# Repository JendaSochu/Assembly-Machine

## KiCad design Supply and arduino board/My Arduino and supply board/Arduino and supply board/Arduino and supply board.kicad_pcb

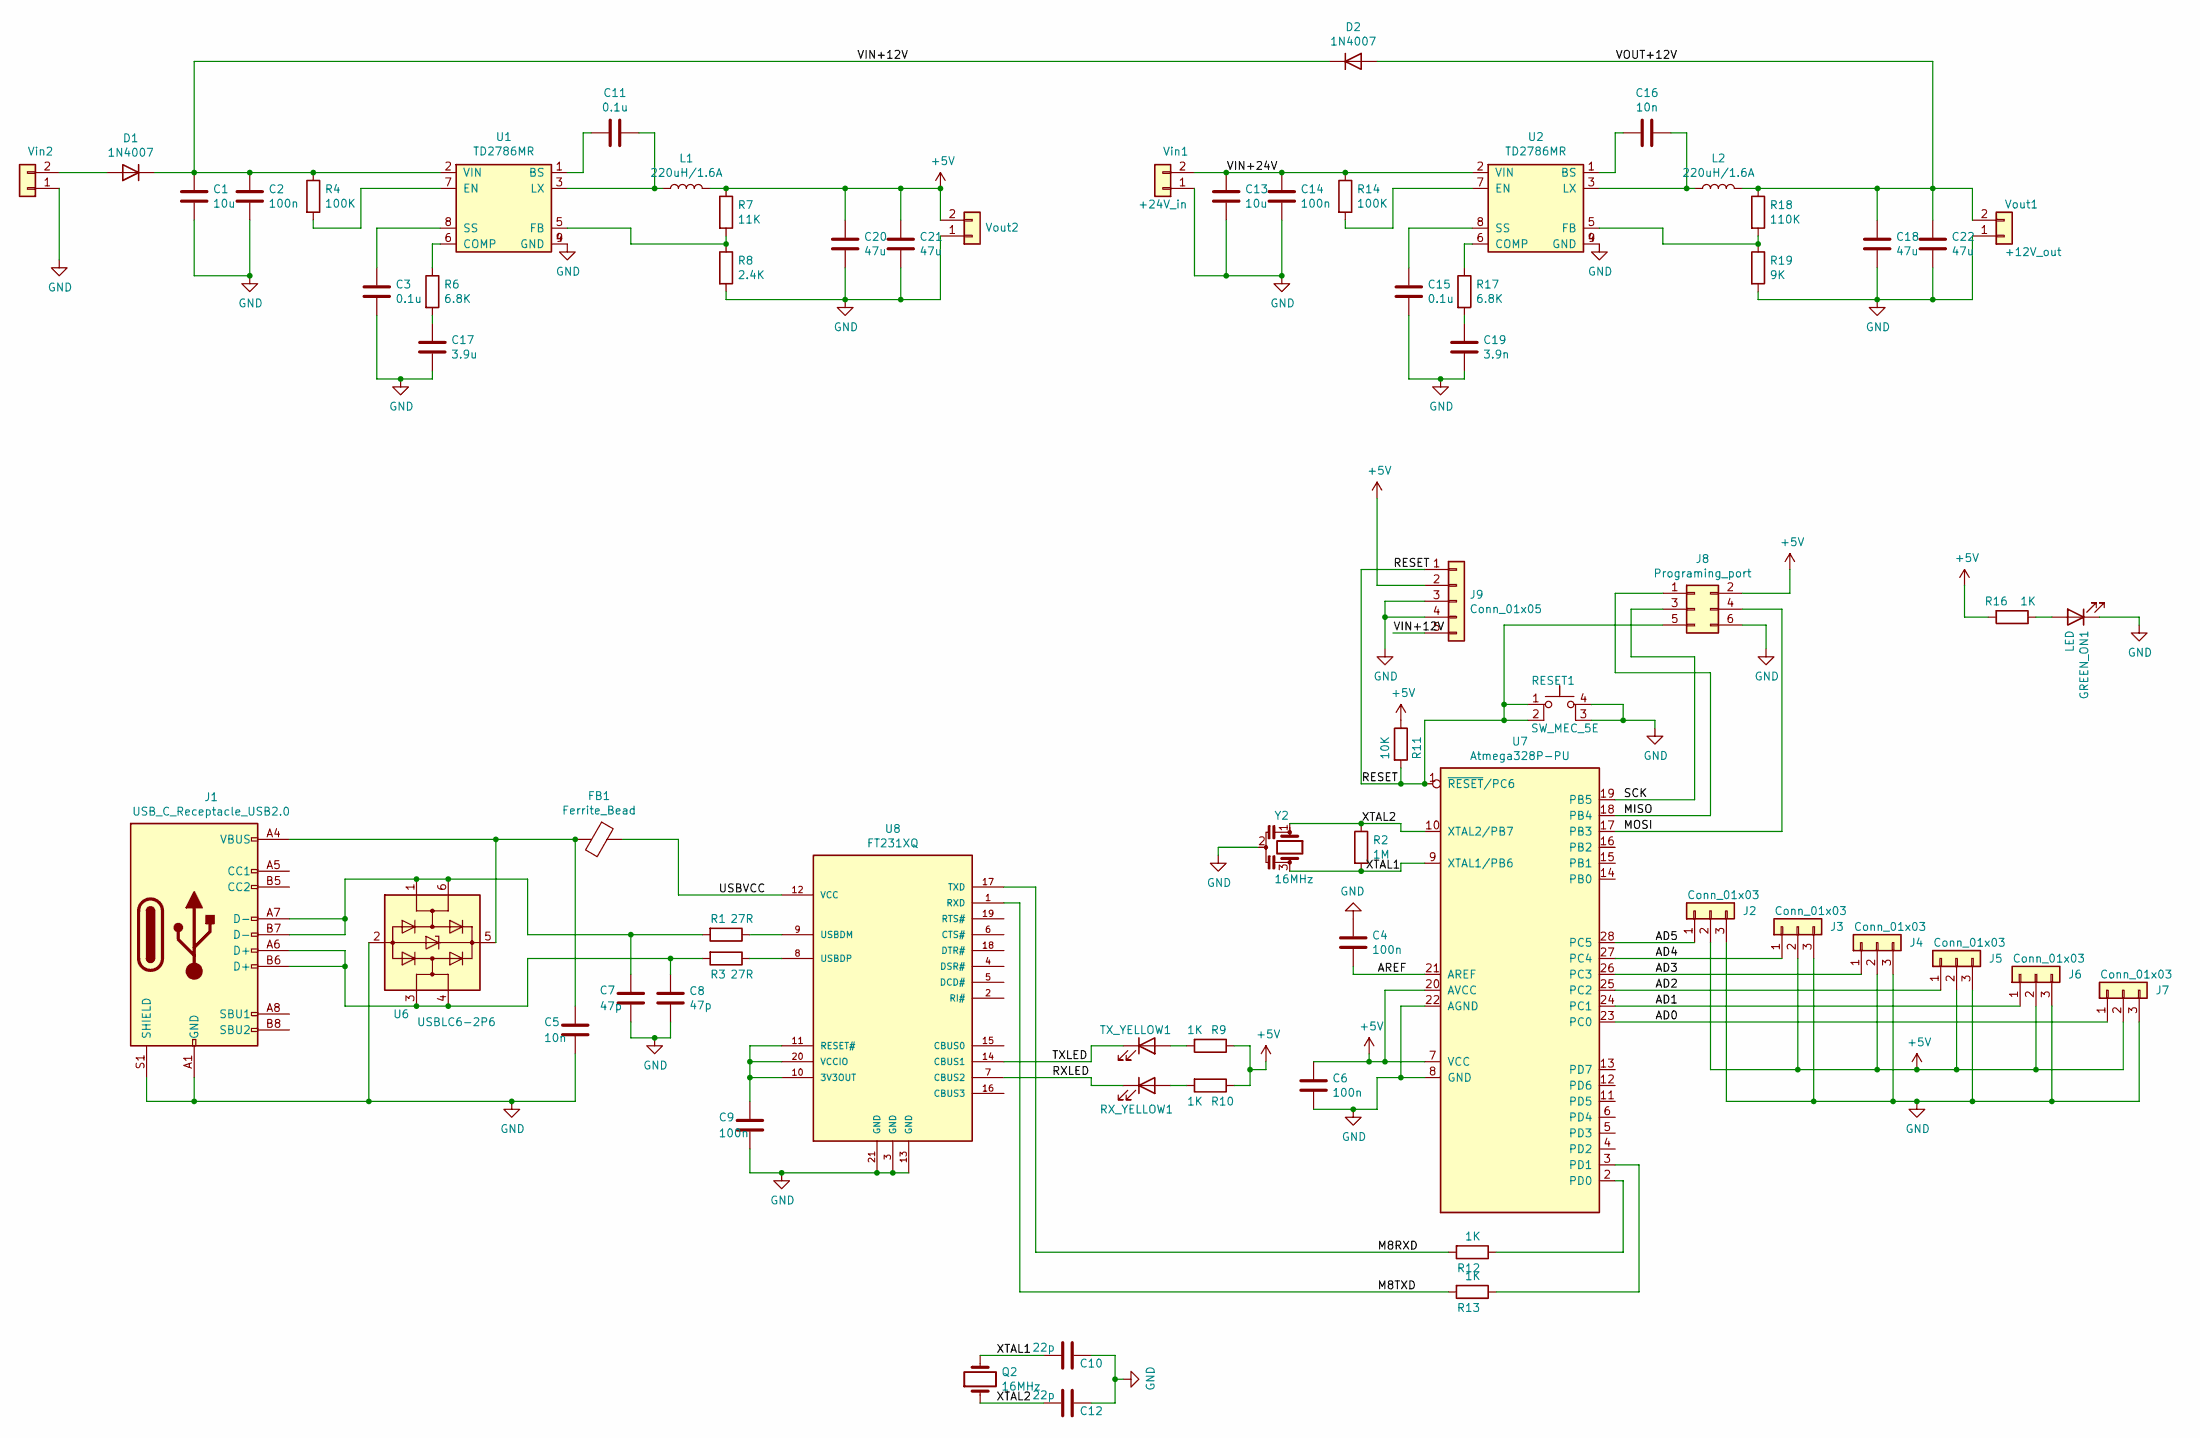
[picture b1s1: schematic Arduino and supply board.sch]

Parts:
C1, C13: 10u; C_0603_1608Metric
C2, C4, C6, C9, C14: 100n; C_0603_1608Metric
C3, C11, C15: 0.1u; C_0603_1608Metric
C5, C16: 10n; C_0603_1608Metric
C7, C8: 47p; C_0603_1608Metric
C10, C12: 22p; C_0603_1608Metric
C17: 3.9u; C_0603_1608Metric
C18, C20, C21, C22: 47u; C_0603_1608Metric
C19: 3.9n; C_0603_1608Metric
D1, D2: 1N4007; D_SMA
FB1: Ferrite_Bead; R_0603_1608Metric
GREEN_ON1: LED; LED_0805_2012Metric
J1: USB_C_Receptacle_USB2.0; USB_C_Receptacle_HRO_TYPE-C-31-M-12
J2, J3, J4, J5, J6, J7: Conn_01x03; PinSocket_1x03_P2.54mm_Vertical
J8: Programing_port; PinHeader_2x03_P2.54mm_Vertical
J9: Conn_01x05; PinHeader_1x05_P2.54mm_Vertical
L1, L2: 220uH/1.6A; L_Wuerth_HCI-1350
Q2: 16MHz; Crystal_HC18-U_Vertical
R1, R3: 27R; R_0402_1005Metric
R2: 1M; R_0402_1005Metric
R4, R14: 100K; R_0402_1005Metric
R6, R17: 6.8K; R_0402_1005Metric
R7: 11K; R_0402_1005Metric
R8: 2.4K; R_0402_1005Metric
R9, R10, R12, R13, R16: 1K; R_0402_1005Metric
R11: 10K; R_0402_1005Metric
R18: 110K; R_0402_1005Metric
R19: 9K; R_0402_1005Metric
RESET1: SW_MEC_5E; SW_DIP_SPSTx02_Slide_6.7x6.64mm_W6.73mm_P2.54mm_LowProfile_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
RX_YELLOW1: LED; LED_0805_2012Metric
TX_YELLOW1: LED; LED_0805_2012Metric
U1, U2: TD2786MR; SOP-8_3.9x4.9mm_P1.27mm
U6: USBLC6-2P6; SOT-666
U7: Atmega328P-PU; TQFP-32_7x7mm_P0.8mm
U8: FT231XQ; QFN-20-1EP_4x4mm_P0.5mm_EP2.5x2.5mm; PARTREV 1.2
Vin1: +24V_in; PhoenixContact_MSTBA_2,5_2-G-5,08_1x02_P5.08mm_Horizontal
Vin2: +12V_in; PhoenixContact_MSTBA_2,5_2-G-5,08_1x02_P5.08mm_Horizontal
Vout1: +12V_out; PhoenixContact_MSTBA_2,5_2-G-5,08_1x02_P5.08mm_Horizontal
Vout2: +5V_out; PhoenixContact_MSTBA_2,5_2-G-5,08_1x02_P5.08mm_Horizontal
Y2: 16MHz; Resonator_SMD-3Pin_7.2x3.0mm

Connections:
+5V: C6.1, C20.2, C21.2, J2.2, J3.2, J4.2, J5.2, J6.2, J7.2, J8.2, J9.2, L1.2, R7.1, R9.1, R10.1, R11.1, R16.2, U7.7 (VCC), U7.20 (AVCC), Vout2.2
/AD0: J7.1, U7.23 (PC0)
/AD1: J6.1, U7.24 (PC1)
/AD2: J5.1, U7.25 (PC2)
/AD3: J4.1, U7.26 (PC3)
/AD4: J3.1, U7.27 (PC4)
/AD5: J2.1, U7.28 (PC5)
/AREF: C4.2, U7.21 (AREF)
/M8RXD: R12.2, U8.17 (TXD)
/M8TXD: R13.2, U8.1 (RXD)
/MISO: J8.1, U7.18 (PB4)
/MOSI: J8.4, U7.17 (PB3)
/RESET: J8.5, J9.1, R11.2, RESET1.1, RESET1.2, U7.1 (~RESET~/PC6)
/RXLED: RX_YELLOW1.1 (K), U8.7 (CBUS2)
/SCK: J8.3, U7.19 (PB5)
/TXLED: TX_YELLOW1.1 (K), U8.14 (CBUS1)
/USBVCC: FB1.1, U8.12 (VCC)
/VIN+12V: C1.1, C2.1, D1.1 (K), D2.1 (K), J9.5, R4.1, U1.2 (VIN)
/VIN+24V: C13.1, C14.1, R14.1, U2.2 (VIN), Vin1.2
/VOUT+12V: C18.2, C22.2, D2.2 (A), L2.2, R18.1, Vout1.2
/XTAL1: C10.1, Q2.2, R2.2, U7.9 (XTAL1/PB6), Y2.3
/XTAL2: C12.1, Q2.1, R2.1, U7.10 (XTAL2/PB7), Y2.1
GND: C1.2, C2.2, C3.2, C4.1, C5.2, C6.2, C7.2, C8.2, C9.2, C10.2, C12.2, C13.2, C14.2, C15.2, C17.2, C18.1, C19.2, C20.1, C21.1, C22.1, GREEN_ON1.1 (K), J1.A1 (GND), J1.A12 (GND), J1.B1 (GND), J1.B12 (GND), J1.S1 (SHIELD), J2.3, J3.3, J4.3, J5.3, J6.3, J7.3, J8.6, J9.3, J9.4, R8.2, R19.2, RESET1.3 (K), RESET1.4 (A), U1.4 (GND), U1.9 (GND), U2.4 (GND), U2.9 (GND), U6.2 (GND), U7.8 (GND), U7.22 (AGND), U8.3 (GND), U8.13 (GND), U8.21 (GND), Vin1.1, Vin2.1, Vout1.1, Vout2.1, Y2.2
unnamed: C3.1, U1.8 (SS)
unnamed: C5.1, FB1.2, J1.A4 (VBUS), J1.A9 (VBUS), J1.B4 (VBUS), J1.B9 (VBUS), U6.5 (VBUS)
unnamed: C7.1, J1.A7 (D-), J1.B7 (D-), R1.2, U6.1 (I/O1), U6.6 (I/O1)
unnamed: C8.1, J1.A6 (D+), J1.B6 (D+), R3.2, U6.3 (I/O2), U6.4 (I/O2)
unnamed: C9.1, U8.10 (3V3OUT), U8.11 (RESET#), U8.20 (VCCIO)
unnamed: C11.1, L1.1, U1.3 (LX)
unnamed: C11.2, U1.1 (BS)
unnamed: C15.1, U2.8 (SS)
unnamed: C16.1, L2.1, U2.3 (LX)
unnamed: C16.2, U2.1 (BS)
unnamed: C17.1, R6.2
unnamed: C19.1, R17.2
unnamed: D1.2 (A), Vin2.2
unnamed: GREEN_ON1.2 (A), R16.1
unnamed: R1.1, U8.9 (USBDM)
unnamed: R3.1, U8.8 (USBDP)
unnamed: R4.2, U1.7 (EN)
unnamed: R6.1, U1.6 (COMP)
unnamed: R7.2, R8.1, U1.5 (FB)
unnamed: R9.2, TX_YELLOW1.2 (A)
unnamed: R10.2, RX_YELLOW1.2 (A)
unnamed: R12.1, U7.2 (PD0)
unnamed: R13.1, U7.3 (PD1)
unnamed: R14.2, U2.7 (EN)
unnamed: R17.1, U2.6 (COMP)
unnamed: R18.2, R19.1, U2.5 (FB)

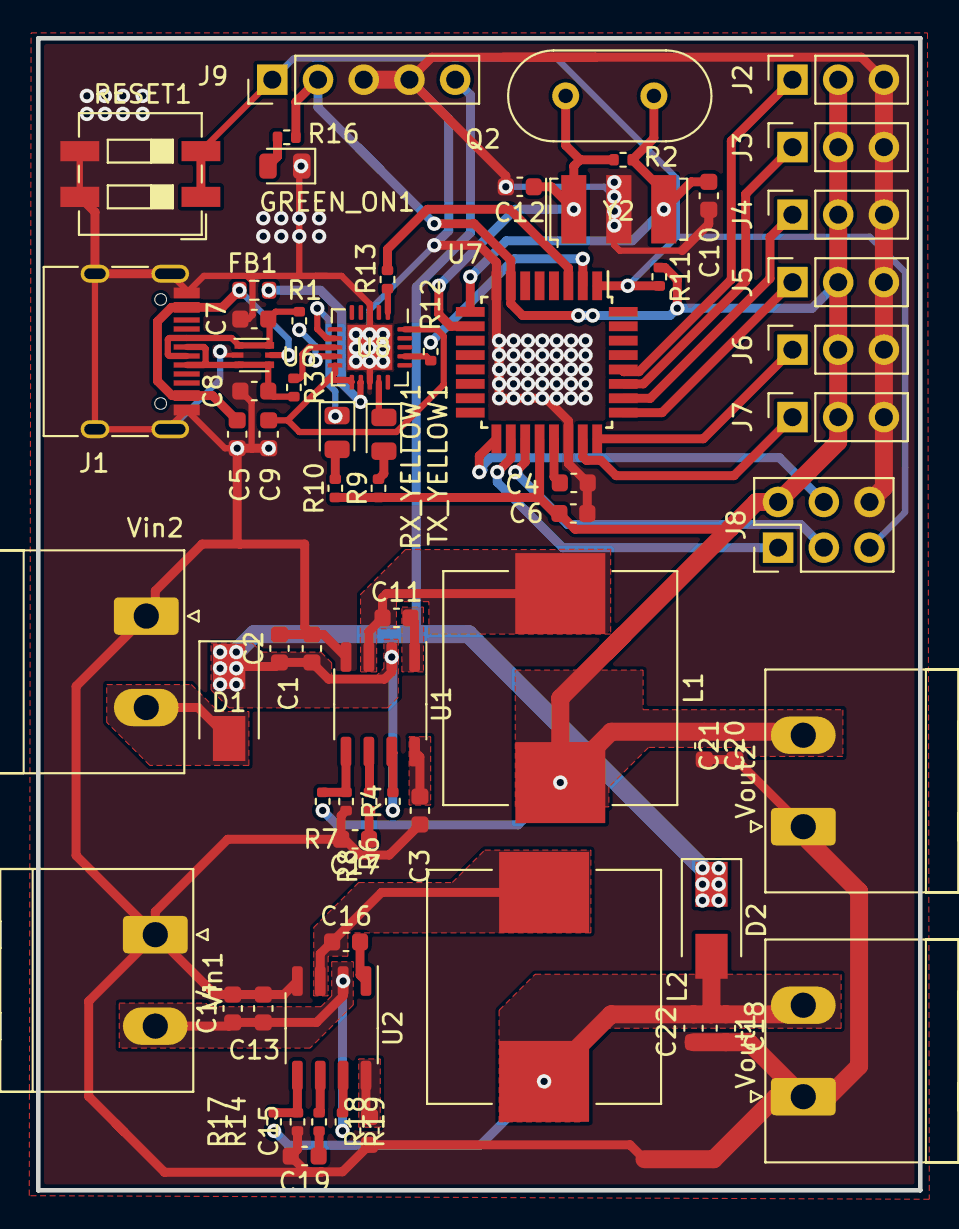
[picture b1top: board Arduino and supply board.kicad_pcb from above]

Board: 2 copper layers, 49.0 x 64.0 mm, 68 parts (0 on the bottom side), 49 nets.

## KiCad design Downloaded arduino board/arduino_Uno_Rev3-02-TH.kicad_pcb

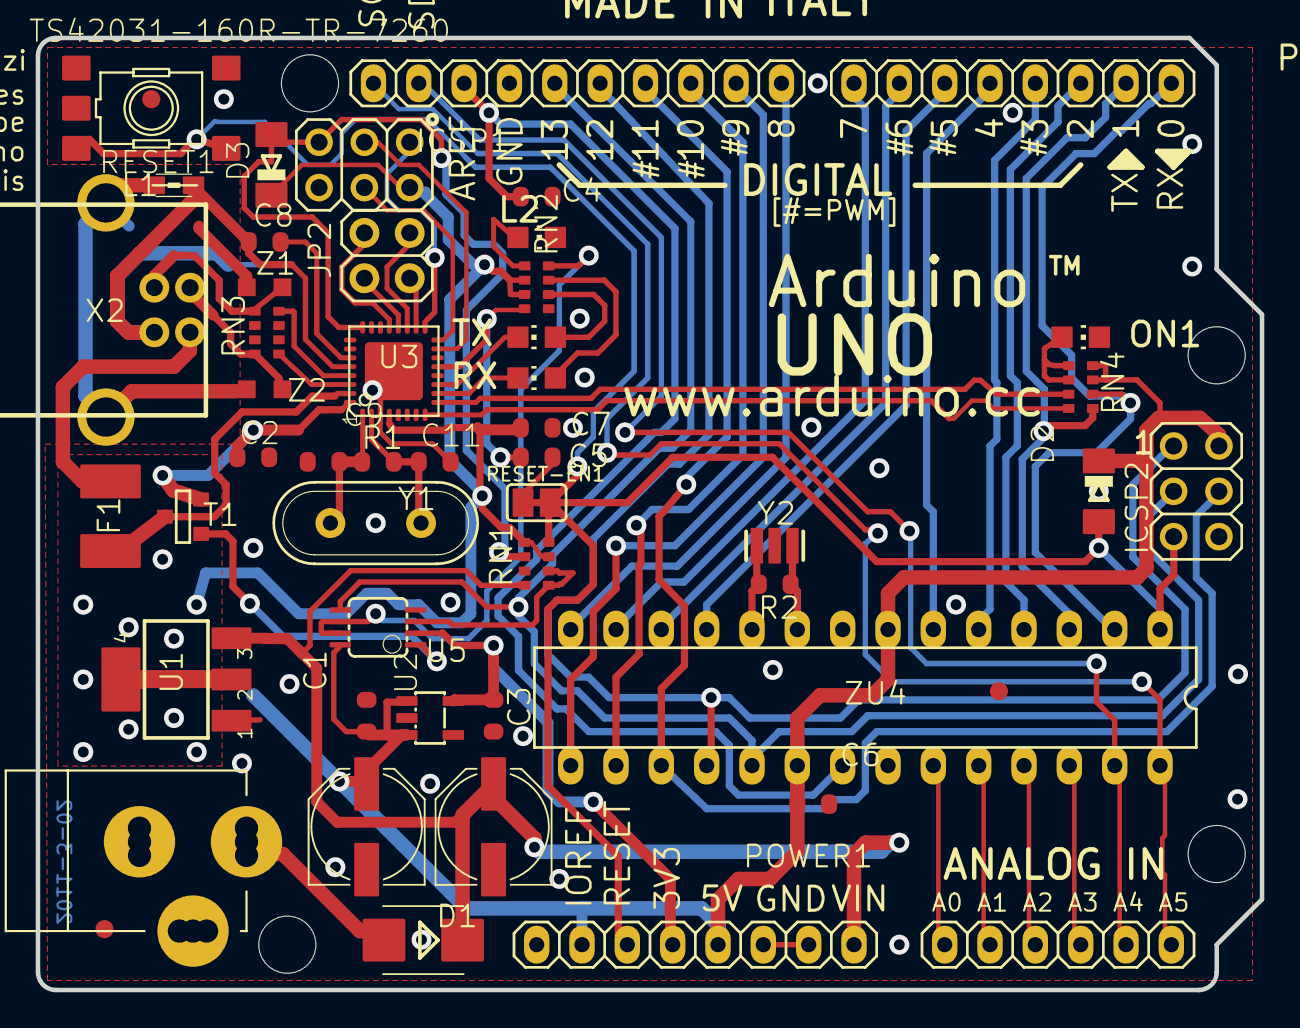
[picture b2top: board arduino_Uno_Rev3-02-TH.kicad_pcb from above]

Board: 2 copper layers, 68.6 x 53.3 mm, 57 parts (0 on the bottom side), 57 nets.

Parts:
@HOLE0, @HOLE1, @HOLE2, @HOLE3: (no value)
AD1: 6x1F-H8.5; 1X06
C1, C2, C4, C5, C6, C7: 100n; C0603-ROUND
C3, C8: 1u; C0603-ROUND
C9, C11: 22p; C0603-ROUND
D1: M7; SMB
D2, D3: CD1206-S01575; MINIMELF
F1: MF-MSMF050-2 500mA; L1812
FD1, FD2, FD3: FIDUCIALMOUNT; FIDUCIA-MOUNT
GROUND1: SJ
ICSP1, ICSP2: 3x2 M; 2X03
IOH: 10x1F-H8.5; 1X10@1
IOL1: 8x1F-H8.5; 1X08
JP2: 2x2 M - NM; 2X02
L1: BLM21; 0805
L2: YELLOW; CHIP-LED0805
ON1: GREEN; CHIP-LED0805
PC1, PC2: 47u; PANASONIC_D
POWER1: 8x1F-H8.5; 1X08
R1, R2: 1M; R0603-ROUND
RESET1: TS42031-160R-TR-7260; TS42
RESET-EN1: SJ
RN1: 10K; CAY16
RN2, RN4: 1K; CAY16
RN3: 22R; CAY16
RX1: YELLOW; CHIP-LED0805
T1: FDN340P; SOT-23
TX1: YELLOW; CHIP-LED0805
U1: NCP1117ST50T3G; SOT223
U2: LP2985-33DBVR; SOT23-DBV
U3: ATMEGA16U2-MU(R); MLF32
U5: LMV358IDGKR; MSOP08
U$1: DISCLAIMER
X1: POWERSUPPLY_DC21MMX; POWERSUPPLY_DC-21MM
X2: USB-B_TH; PN61729
Y1: 16MHz; QS
Y2: CSTCE16M0V53-R0 16MHZ; RESONATOR
Z1, Z2: CG0603MLC-05E; CT_CN0603
ZU4: ATMEGA328P-PU; DIL28-3

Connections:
+5V: C1.2, C2.2, C6.2, C7.1, D2.C, D3.C, ICSP1.2, ICSP2.2, PC2.+, POWER1.2, POWER1.5, RN1.3, RN1.5, RN2.2, RN2.3, RN4.3, RN4.4, T1.2, U1.2, U1.4, U2.1, U2.3, U3.4, U3.32, U5.8, ZU4.7, ZU4.20
/+3V3: C3.2, POWER1.4, U2.5, U5.2
/AD0: AD1.1, ZU4.23
/AD1: AD1.2, ZU4.24
/AD2: AD1.3, ZU4.25
/AD3: AD1.4, ZU4.26
/AD4/SDA: AD1.5, ZU4.27
/AD5/SCL: AD1.6, ZU4.28
/AREF: C4.2, ZU4.21
/CMP: RN1.1, RN1.2, U5.3
/D+: RN3.5, X2.3, Z1.1
/D-: RN3.8, X2.2, Z2.1
/DTR: C5.1, RN2.4, U3.13
/GATE_CMD: T1.3, U5.1
/IO0: IOL1.1, RN4.2, ZU4.2
/IO1: IOL1.2, RN4.1, ZU4.3
/IO2: IOL1.3, ZU4.4
/IO3: IOL1.4, ZU4.5
/IO4: IOL1.5, ZU4.6
/IO5: IOL1.6, ZU4.11
/IO6: IOL1.7, ZU4.12
/IO7: IOL1.8, ZU4.13
/L13: RN2.8, U5.6, U5.7
/M8RXD: RN4.7, U3.9
/M8TXD: RN4.8, U3.8
/MISO: ICSP2.1, ZU4.18
/MISO2: ICSP1.1, U3.17
/MOSI: ICSP2.4, ZU4.17
/MOSI2: ICSP1.4, U3.16
/PB4: JP2.1, U3.18
/PB5: JP2.3, U3.19
/PB6: JP2.2, U3.20
/PB7: JP2.4, U3.21
/PWRIN: D1.A, X1.2
/RD+: RN3.4, U3.29
/RD-: RN3.1, U3.30
/RESET: C5.2, D2.A, ICSP2.5, POWER1.3, RESET1.3, RESET1.4, RESET-EN1.1, RESET-EN1.2, RN1.4, ZU4.1
/RESET2: D3.A, ICSP1.5, RN1.6, U3.24
/RXLED: RX1.C, U3.10
/SCK: ICSP2.3, U5.5, ZU4.19
/SCK2: ICSP1.3, U3.15
/TP_VUCAP: C8.1, U3.27
/TXLED: TX1.C, U3.11
/UGND: C8.2, GROUND1.2, L1.1, U3.28, X2.4
/USBVCC: F1.1, T1.1, U3.31
/USHIELD: L1.2, X2.P$1, X2.P$2, Z1.2, Z2.2
/VIN: D1.C, PC1.+, POWER1.8, RN1.8, U1.3
/XT1: C9.1, R1.1, U3.1, Y1.2
/XT2: C11.1, R1.2, U3.2, Y1.1
/XTAL1: R2.1, Y2.3, ZU4.9
/XTAL2: R2.2, Y2.1, ZU4.10
/XUSB: F1.2, X2.1
GND: C1.1, C2.1, C3.1, C4.1, C6.1, C7.2, C9.2, C11.2, GROUND1.1, ICSP1.6, ICSP2.6, IOH.7, L2.C, ON1.C, PC1.-, PC2.-, POWER1.6, POWER1.7, RESET1.1, RESET1.2, RN1.7, RN2.5, U1.1, U2.2, U3.3, U3.33, U5.4, X1.1, X1.3, Y2.2, ZU4.8, ZU4.22
unnamed: L2.A, RN2.1
unnamed: ON1.A, RN4.5, RN4.6
unnamed: RN2.6, TX1.A
unnamed: RN2.7, RX1.A

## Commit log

2023-10-11 (agenda) new todo list
2023-10-18 (agenda) updated todo list
2023-10-25 (agenda) updated todo list. going through issues and solutions
2023-11-06 Create Important links
2023-11-06 Rename Important links to Important links.md
2023-11-23 add marlin firmware for my assembly machine and 3D parts for feader for lose parts
2023-11-23 new .zip file with lose part feeder 3D models
2023-11-24 new file for work on arduino and supply board
2023-11-24 new folder downloaded arduino board with downloaded arduino scheme and board
2023-11-24 new kicad files with start work on my arduino board
2023-11-28 work on my arduino and supply board
2023-11-29 new work on Arduino and supply board
2023-11-30 work on arduino board, every components have package
2023-12-04 new work on arduino board
2023-12-04 every part on board is connected
2023-12-06 new work on board
2023-12-10 big changes on arduino board
2023-12-11 work on arduino board
2023-12-12 add usb protect
2023-12-14 add text on PCB
2023-12-19 new DC-DC power supply
2023-12-19 change power supply 24v to 12v and 12v to 5v
2023-12-26 generate blueprints for lose part feeder
2023-12-27 changes on powersuply
2023-12-27 generate images off board
